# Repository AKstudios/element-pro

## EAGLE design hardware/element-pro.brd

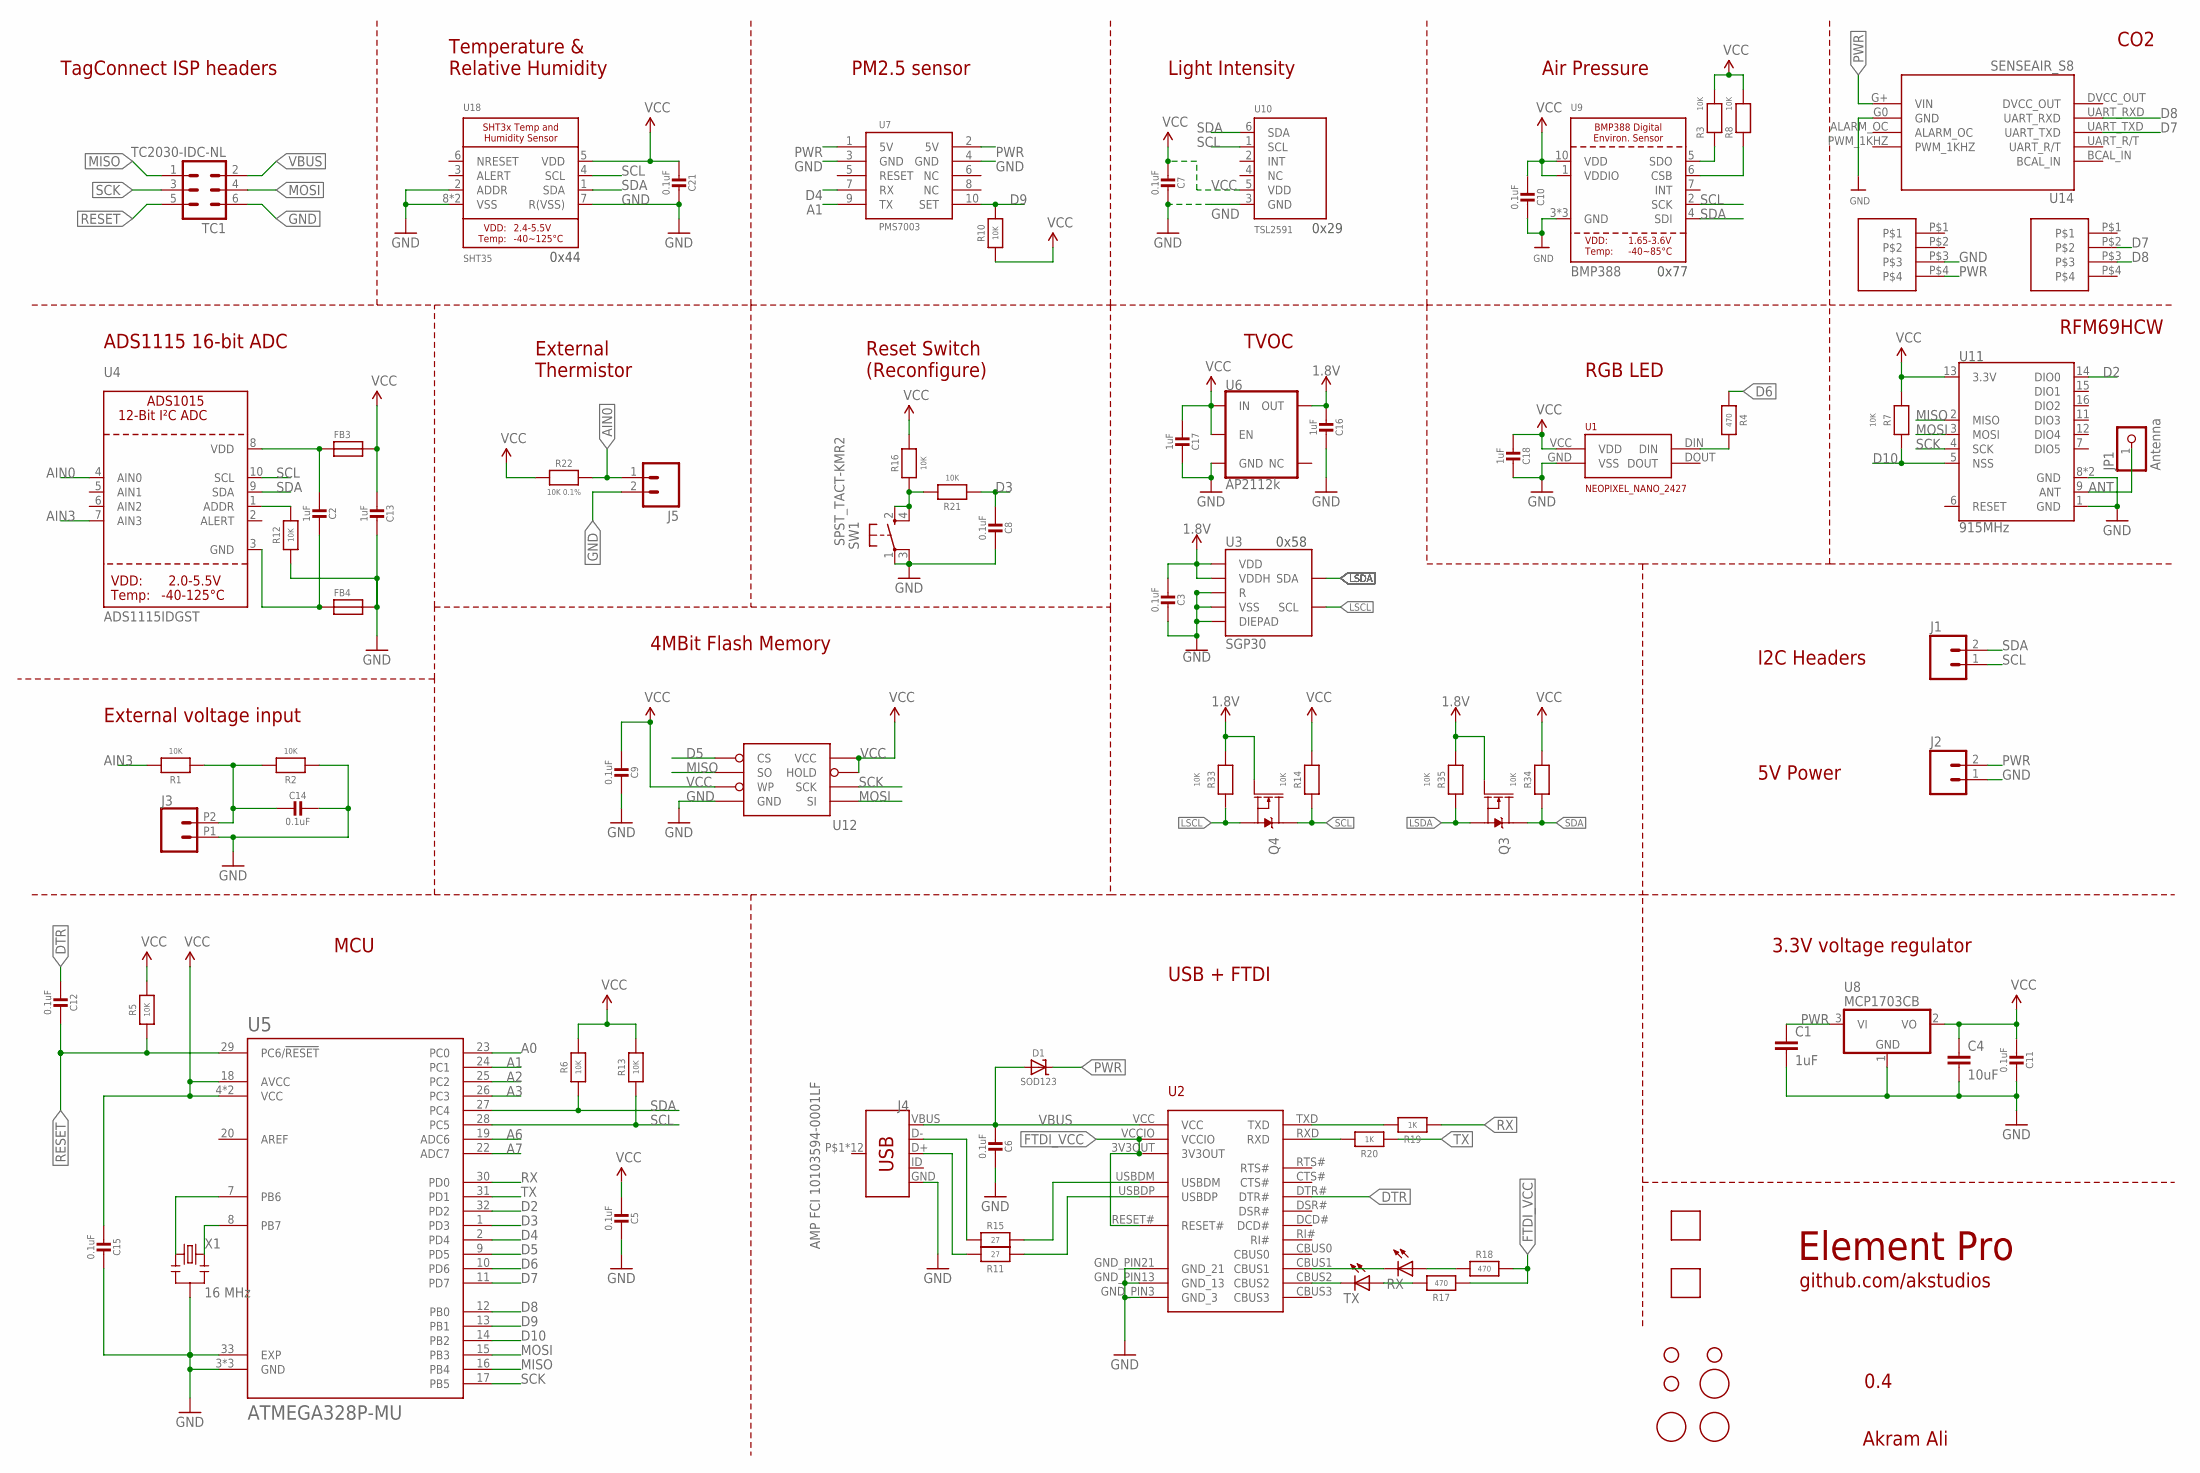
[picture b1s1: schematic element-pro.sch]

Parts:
C1: 1uF; 0805@1; MPN CC0805ZRY5V8BB105
C2, C13, C16, C17: 1uF; MICROBUILDER__0402MP; MPN GRM155R71C104KA88J
C3, C5, C6, C7, C8, C9, C10, C11, C12, C14, C15, C21: 0.1uF; MICROBUILDER__0402MP; MPN GRM155R71C104KA88J
C4: 10uF; 0805@1; MPN CC0805KKX5R6BB106
C18: 1uF; MICROBUILDER__0402MP; MPN CC0402KRX5R6BB105
D1: SOD123; MICROBUILDER_SOD-123; MPN SD103AW-13-F
FB3, FB4: FERRITE0402; 0402
H1, H2, H3: STAND-OFF
J1, J2, J5: M02PTH; 1X02@1
J3: CONN_022.54MM_SCREWTERM; 1X02_2.54_SCREWTERM
J4: AMP FCI 10103594-0001LF; USB-MICROB-PTH
JP1: Antenna; 1X01-CLEANBIG; MPN Helical antenna
Q3, Q4: BSS138PW,115; SOT323
R1, R2, R3, R5, R6, R7, R8, R10, R12, R13, R14, R16, R21, R33, R34, R35: 10K; MICROBUILDER__0402MP; MPN RC0402JR-0710KL
R4, R17, R18: 470; MICROBUILDER__0402MP; MPN RC0402JR-07470RL
R11, R15: 27; MICROBUILDER__0402MP; MPN RC0402JR-0727RL
R19, R20: 1K; MICROBUILDER__0402MP; MPN RC0402JR-071KL
R22: 10K 0.1%; MICROBUILDER__0402MP; MPN RC0402JR-0727RL
RX: LEDCHIPLED_0805; CHIPLED_0805; MPN LG R971-KN-1
SW1: SPST_TACT-KMR2; KMR2
TC1: TC2030-IDC-NL
TX: LEDCHIPLED_0805; CHIPLED_0805; MPN LG R971-KN-1
U1: NEOPIXEL_NANO_2427; SK6805-2427; MPN 3484
U2: FT231XQ-R; FTDI_FT231XQ-R_PACKAGE; MPN FT231XQ-R
U3: SGP30
U4: ADS1115IDGST; MSOP10
U5: ATMEGA328P-MU; QFN50P500X500X100-33N; MPN ATMEGA328P-MU
U6: AP2112k; SOT23-5
U7: PMS7003; PMS7003_RECEPTACLE_1.27MM_2X5; MPN 20021311-00012T4LF
U8: MCP1703CB; SOT23; MPN MCP1703T-3302E/CB
U9: BMP388
U10: TSL2591; DFN6_TAOS; MPN TSL25911FN
U11: 915MHz; RFM69HCW-XXXS2; MPN RFM69HCW
U12: W25X40CLSNIG-ND-AT25F512BJEDEC_3.9MM; SO08
U14: SENSEAIR_S8
U15: VLP-450-F; MPN VLP-650-F
U16: VLP-450-F; MPN VLP-550-F
U18: SHT35; SHT3X; MPN SHT35-DIS-B
U$1, U$2, U$3: FIDUCIAL; FIDUCIAL_1MM
U$4, U$5: 0878980426; CONN_4POS_VERT_2.54_SMD; MPN 0878980426
X1: 16 MHz; RESONATOR-SMD; MPN CSTCE16M0V53-R0

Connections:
1.8V: C3.2, C16.2, Q3.1 (G), Q4.1 (G), R33.2, R35.2, U3.1 (VDD), U3.5 (VDDH), U6.5 (OUT)
A0: U5.23 (PC0)
A1: U5.24 (PC1), U7.9 (TX)
A2: U5.25 (PC2)
A3: U5.26 (PC3)
A6: U5.19 (ADC6)
A7: U5.22 (ADC7)
ADDR: R12.2, U4.1 (ADDR)
ADR: R3.1, U9.5 (SDO)
AIN0: J5.1, R22.2, U4.4 (AIN0)
AIN3: R1.2, U4.7 (AIN3)
ANT: JP1.1, U11.9 (ANT)
CS: R8.1, U9.6 (CSB)
D2: U5.32 (PD2), U11.14 (DIO0)
D3: C8.2, R21.1, U5.1 (PD3)
D4: U5.2 (PD4), U7.7 (RX)
D5: U5.9 (PD5), U12.1_CS (CS)
D6: R4.1, U5.10 (PD6)
D7: U5.11 (PD7), U14.UART_TXD, U$5.P$2
D8: U5.12 (PB0), U14.UART_RXD, U$5.P$3
D9: R10.2, U5.13 (PB1), U7.10 (SET)
D10: R7.1, U5.14 (PB2), U11.5 (NSS)
DTR: C12.2, U2.DTR#
FTDI_VCC: R17.1, R18.2, U2.3V3OUT, U2.RESET#, U2.VCCIO
GND: C1.2, C3.1, C4.2, C5.1, C6.1, C7.1, C8.1, C9.1, C10.1, C11.1, C13.1, C14.1, C15.1, C16.1, C17.1, C18.1, C21.1, FB4.2, J2.1, J3.P1 (1), J4.GND, J5.2, R2.1, R12.1, SW1.1, SW1.3 (P1), TC1.6, U1.GND (VSS), U2.GND_PIN3 (GND_3), U2.GND_PIN13 (GND_13), U2.GND_PIN21 (GND_21), U3.2 (VSS), U3.4 (R), U3.DIEPAD, U5.3 (GND), U5.5 (GND), U5.21 (GND), U5.33 (EXP), U6.2 (GND), U7.3 (GND), U7.4 (GND), U8.1 (GND), U9.3 (GND), U9.8 (GND), U9.9 (GND), U10.3 (GND), U11.1 (GND), U11.8 (GND), U11.10 (GND), U12.4_GND (GND), U14.G0 (GND), U18.2 (ADDR), U18.7 (R(VSS)), U18.8 (VSS), U18.THERMAL (VSS), U$4.P$3, X1.2
LSCL: Q4.2 (S), R33.1, U3.6 (SCL)
LSDA: Q3.2 (S), R35.1, U3.3 (SDA)
MISO: TC1.1, U5.16 (PB4), U11.2 (MISO), U12.2_SO (SO)
MOSI: TC1.4, U5.15 (PB3), U11.3 (MOSI), U12.5_SI (SI)
unnamed: R4.2, U1.DIN
unnamed: R20.2, U2.RXD
unnamed: R19.2, U2.TXD
unnamed: U5.8 (PB7), X1.3
unnamed: U5.7 (PB6), X1.1
unnamed: C14.2, J3.P2 (2), R1.1, R2.2
unnamed: C2.1, FB4.1, U4.3 (GND)
unnamed: C2.2, FB3.1, U4.8 (VDD)
unnamed: R16.1, R21.2, SW1.2 (S), SW1.4 (S1)
unnamed: RX.C, U2.CBUS1
unnamed: TX.C, U2.CBUS2
unnamed: R15.2, U2.USBDM
unnamed: R11.1, U2.USBDP
unnamed: R18.1, RX.A
unnamed: R17.2, TX.A
unnamed: J4.D-, R15.1
unnamed: J4.D+, R11.2
PWR: C1.1, D1.C, J2.2, U7.1 (5V), U7.2 (5V), U8.3 (VI), U14.G+ (VIN), U$4.P$4
RESET: C12.1, R5.1, TC1.5, U5.29 (PC6/!RESET)
RX: R19.1, U5.30 (PD0)
SCK: TC1.3, U5.17 (PB5), U11.4 (SCK), U12.6_SCK (SCK)
SCL: J1.1, Q4.3 (D), R13.1, R14.1, U4.10 (SCL), U5.28 (PC5), U9.2 (SCK), U10.1 (SCL), U18.4 (SCL)
SDA: J1.2, Q3.3 (D), R6.1, R34.1, U4.9 (SDA), U5.27 (PC4), U9.4 (SDI), U10.6 (SDA), U18.1 (SDA)
TX: R20.1, U5.31 (PD1)
VBUS: C6.2, D1.A, J4.VBUS, TC1.2, U2.VCC
VCC: C4.1, C5.2, C7.2, C9.2, C10.2, C11.2, C13.2, C15.2, C17.2, C18.2, C21.2, FB3.2, R3.2, R5.2, R6.2, R7.2, R8.2, R10.1, R13.2, R14.2, R16.2, R22.1, R34.2, U1.VCC (VDD), U5.4 (VCC), U5.6 (VCC), U5.18 (AVCC), U6.1 (IN), U6.3 (EN), U8.2 (VO), U9.1 (VDDIO), U9.10 (VDD), U10.5 (VDD), U11.13 (3.3V), U12.3_WP (WP), U12.7_HOLD (HOLD), U12.8_VCC (VCC), U18.5 (VDD)

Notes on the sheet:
Light Intensity
Air Pressure
4MBit Flash Memory
Temperature & Relative Humidity
TagConnect ISP headers
3.3V voltage regulator
Element Pro
Akram Ali
USB + FTDI
0.4
github.com/akstudios
0x29
RGB LED
I2C Headers
PM2.5 sensor
RFM69HCW
MCU
CO2
TVOC
5V Power
Reset Switch (Reconfigure)
0x58
0x44
0x77
ADS1115 16-bit ADC
External Thermistor
External voltage input

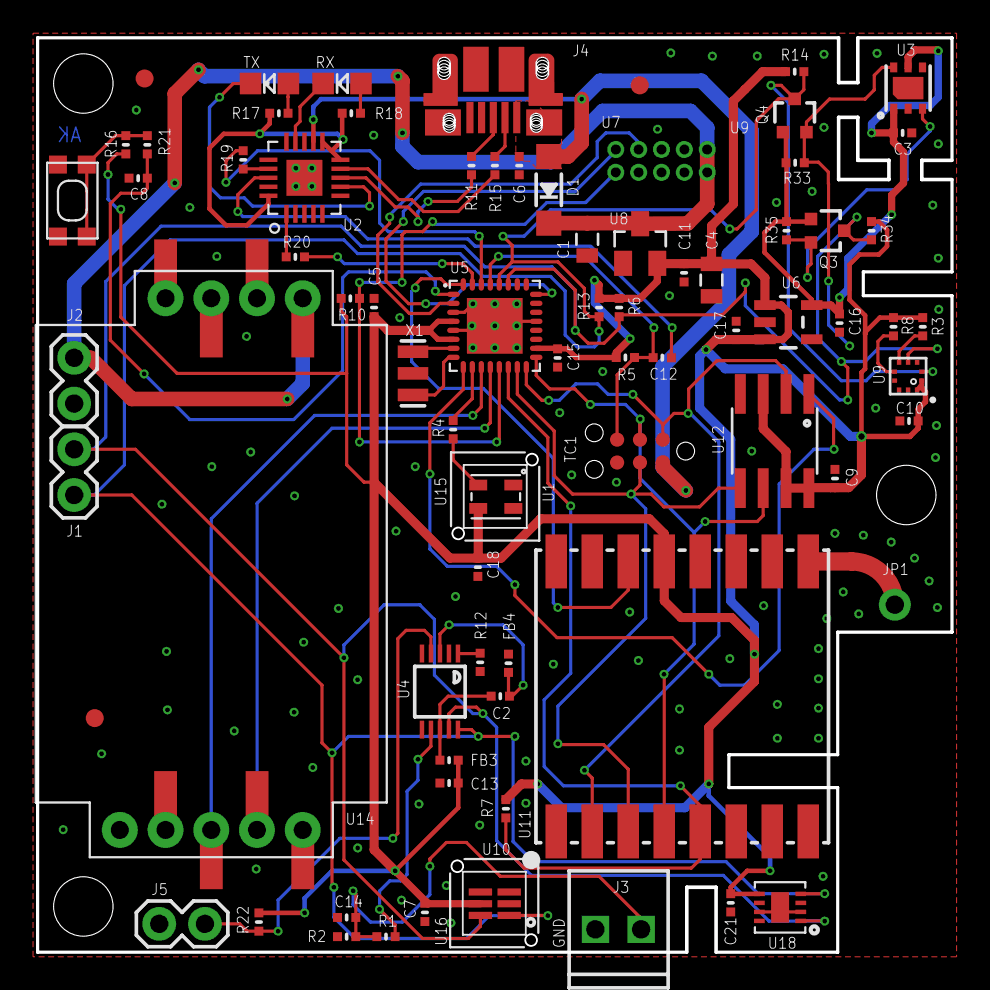
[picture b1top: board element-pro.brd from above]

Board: 2 copper layers, 50.8 x 50.8 mm, 83 parts (1 on the bottom side), 50 nets.

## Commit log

2019-03-03 init
2019-03-03 Create LICENSE
2019-03-03 silkscreen, nibbletz adjustment
2019-03-03 updated swag
2019-05-29 v0.2 - design update
    - moved T/RH sensor away from top
    - moved thermistor + ADC away from top
    - moved VOC sensor from bottom
    - repositioned pressure sensor
    - added more isolation to all necessary sensors
    - a lot of trace and component placement adjustments
2019-05-30 firmware update
2019-06-26 v0.3 update
    moved stuff around a bit - functionalluy the same as before.
2019-06-26 branding modification
2019-06-27 Updated firmware for v0.2
    - PM sensor code still untested - two software serials?
2019-06-28 firmware update
    - added PM sensor enable/disable feature
    - changed external thermistor to external voltage
    - added auto gain for external voltage input
    - fixed CO2 sensor reading
    - fixed temperature reading from thermistor
    - minor changes to final datapacket
2019-07-01 v0.4 - repositioning sensors
    - better heat management
    - added more thermal breaks on board
    - rearranged many traces
    - erc/drc

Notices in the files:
parts and their libraries:
SparkFun-Connectors: Licensing: Creative Commons ShareAlike 4.0 International - https://creativecommons.org/licenses/by-sa/4.0
microbuilder: This work is placed in the public domain, and may be freely used for commercial and non-commercial work with the following conditions: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
